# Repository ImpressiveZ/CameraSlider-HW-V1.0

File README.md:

# CameraSlider-HW-V1.0
滑轨电路板KiCAD工程，V1.0

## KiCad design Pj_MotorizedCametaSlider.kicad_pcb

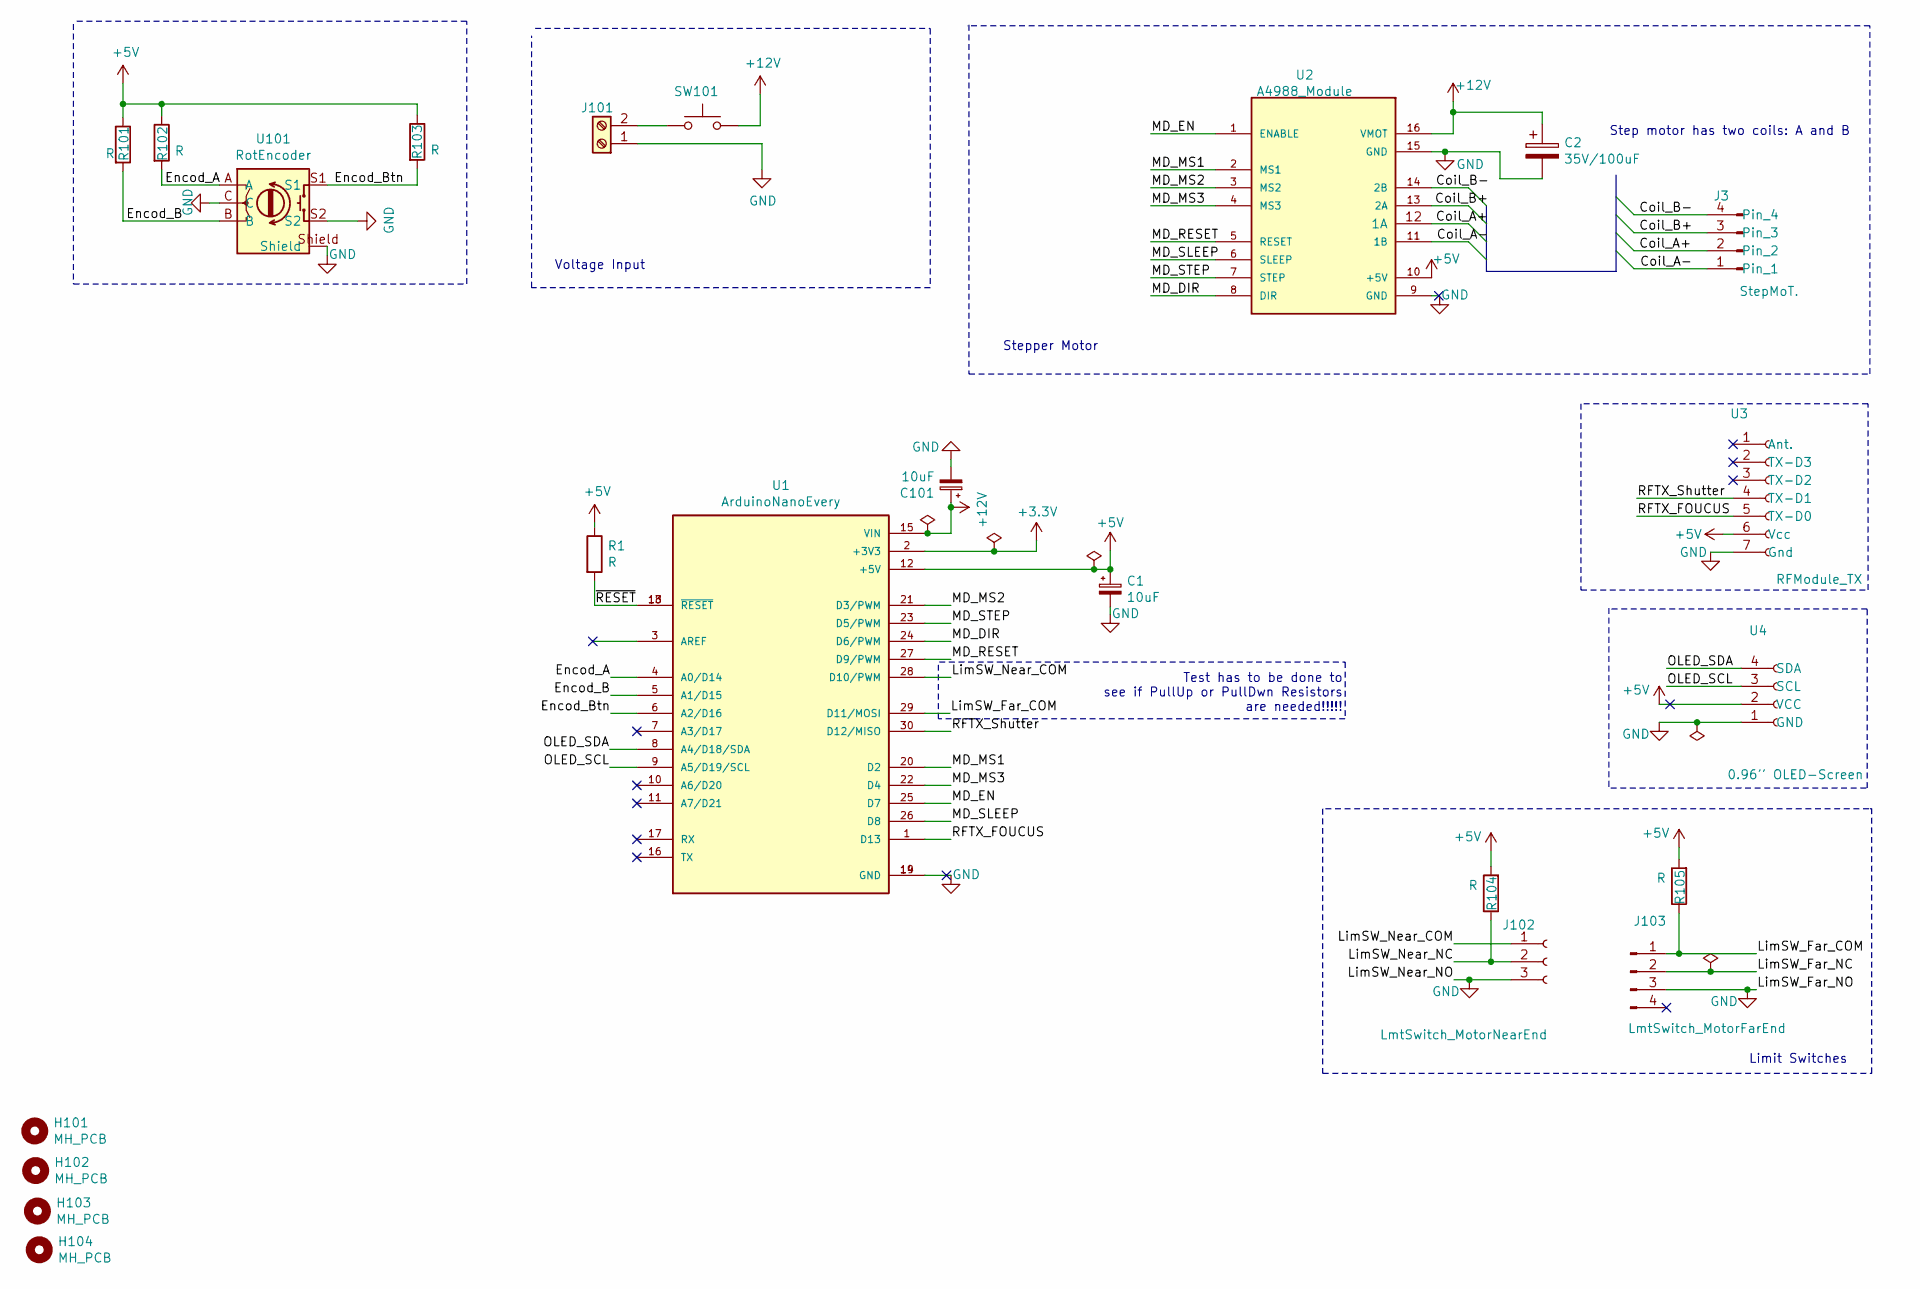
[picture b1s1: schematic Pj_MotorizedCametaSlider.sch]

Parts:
C1, C101: 10uF; CP_Radial_D5.0mm_P2.50mm
C2: 35V/100uF; CP_Radial_D5.0mm_P2.50mm
H101, H102, H103, H104: MH_PCB; MountingHole_3.2mm_M3
J3: StepMoT.; Molex_SPOX_4Pol
J101: Screw_Terminal_01x02; PhoenixContact_MCV_1,5_2-G-5.08_1x02_P5.08mm_Vertical
J102: LmtSwitch_MotorNearEnd; LimitSwitch_3-Pin_MH-included
J103: LmtSwitch_MotorFarEnd; PinHeader_1x04_P2.54mm_Vertical
R1, R101, R102, R103, R104, R105: R; R_0805_2012Metric_Pad1.20x1.40mm_HandSolder
SW101: SW_Push; SW_E-Switch_EG1271_DPDT
U1: ArduinoNanoEvery; MODULE_ArduinoNanoEvery; PARTREV 6-11-19
U2: A4988_Module; Module_A4988
U3: RFModule_TX; PinSocket_1x07_P2.54mm_Vertical
U4: 0.96'' OLED-Screen; 0.96-OLED
U101: RotEncoder

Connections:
+3V3: U1.2 (+3V3)
+5V: C1.1, R1.1, R101.1, R102.1, R103.1, R104.2, R105.2, U1.12 (+5V), U2.10 (+5V), U3.6 (Vcc), U4.2 (VCC)
+12V: C2.1, C101.1, SW101.2, U1.15 (VIN), U2.16 (VMOT); also elsewhere on the board
/Coil_A+: J3.2, U2.12 (1A)
/Coil_A-: J3.1, U2.11 (1B)
/Coil_B+: J3.3, U2.13 (2A)
/Coil_B-: J3.4, U2.14 (2B)
/Encod_A: R102.2, U1.4 (A0/D14), U101.A
/Encod_B: R101.2, U1.5 (A1/D15), U101.B
/Encod_Btn: R103.2, U1.6 (A2/D16), U101.S1
/LimSW_Far_COM: J103.1, R105.1, U1.29 (D11/MOSI)
/LimSW_Far_NC: J103.2
/LimSW_Near_COM: J102.1 (COM), U1.28 (D10/PWM)
/LimSW_Near_NC: J102.2 (NC), R104.1
/MD_DIR: U1.24 (D6/PWM), U2.8 (DIR)
/MD_EN: U1.25 (D7), U2.1 (ENABLE)
/MD_MS1: U1.20 (D2), U2.2 (MS1)
/MD_MS2: U1.21 (D3/PWM), U2.3 (MS2)
/MD_MS3: U1.22 (D4), U2.4 (MS3)
/MD_RESET: U1.27 (D9/PWM), U2.5 (RESET)
/MD_SLEEP: U1.26 (D8), U2.6 (SLEEP)
/MD_STEP: U1.23 (D5/PWM), U2.7 (STEP)
/OLED_SCL: U1.9 (A5/D19/SCL), U4.3 (SCL)
/OLED_SDA: U1.8 (A4/D18/SDA), U4.4 (SDA)
/RFTX_FOUCUS: U1.1 (D13), U3.5 (TX-D0)
/RFTX_Shutter: U1.30 (D12/MISO), U3.4 (TX-D1)
/~RESET: R1.2, U1.13 (~RESET), U1.18 (~RESET)
GND: C1.2, C2.2, C101.2, J101.1, J102.3 (NO), J103.3, U1.14 (GND), U1.19 (GND), U2.9 (GND), U2.15 (GND), U3.7 (Gnd), U4.1 (GND), U101.C, U101.S2, U101.Shield
unnamed 28: J101.2, SW101.1; also elsewhere on the board

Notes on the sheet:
Step motor has two coils: A and B
Voltage Input
Stepper Motor
Test has to be done to see if PullUp or PullDwn Resistors are needed!!!!!
Limit Switches

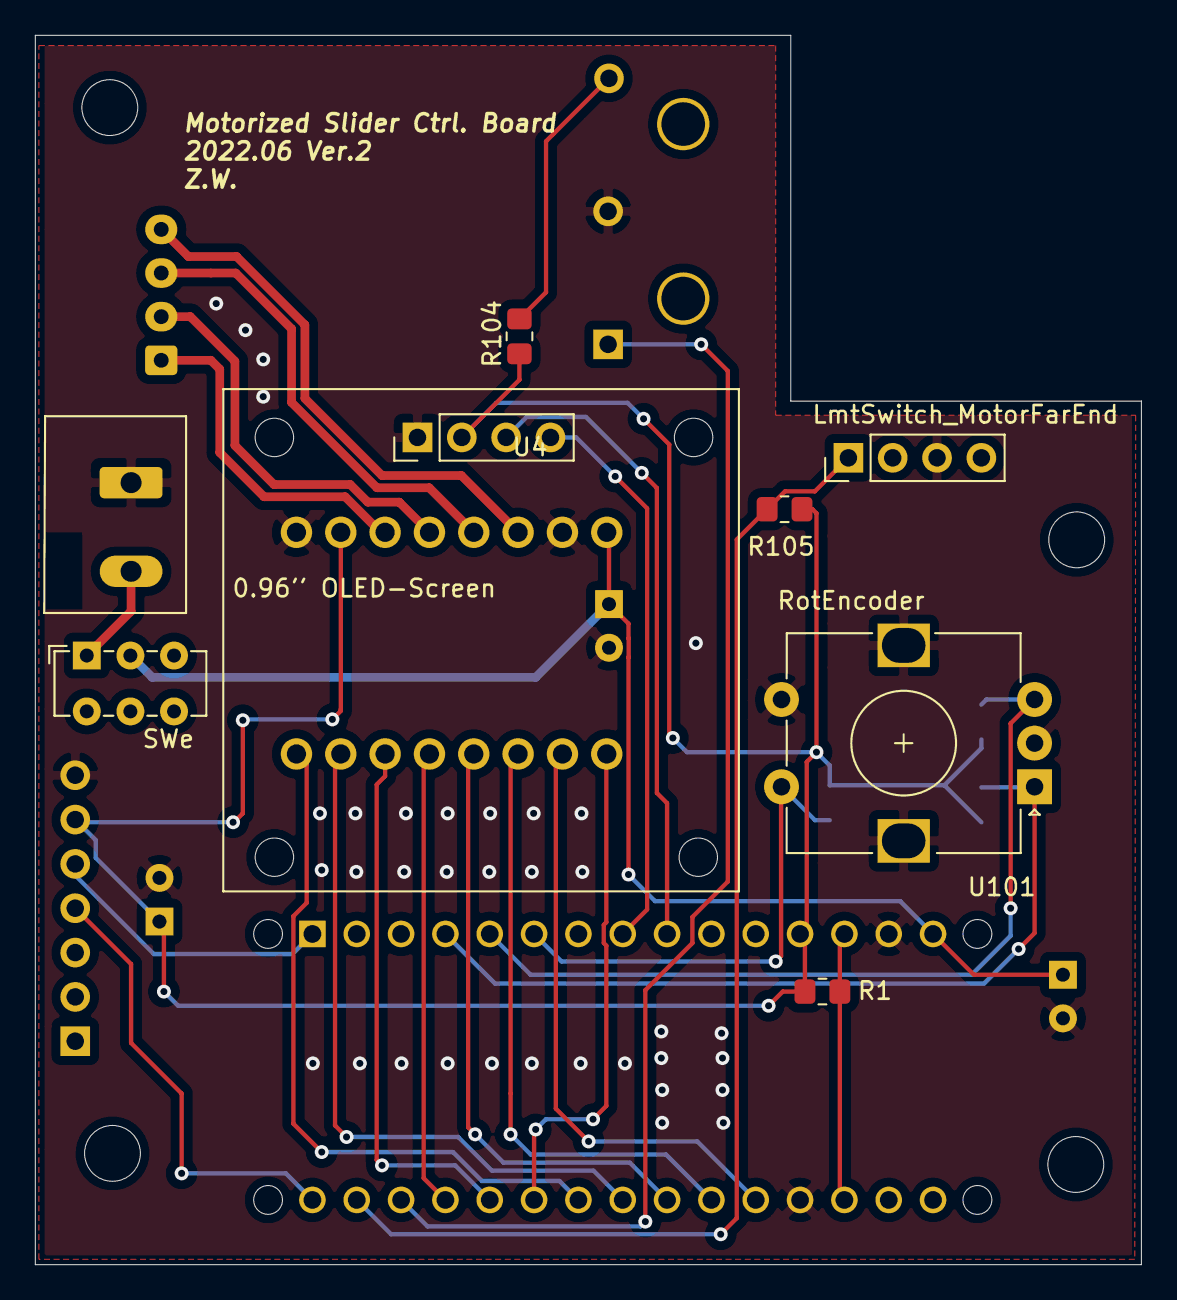
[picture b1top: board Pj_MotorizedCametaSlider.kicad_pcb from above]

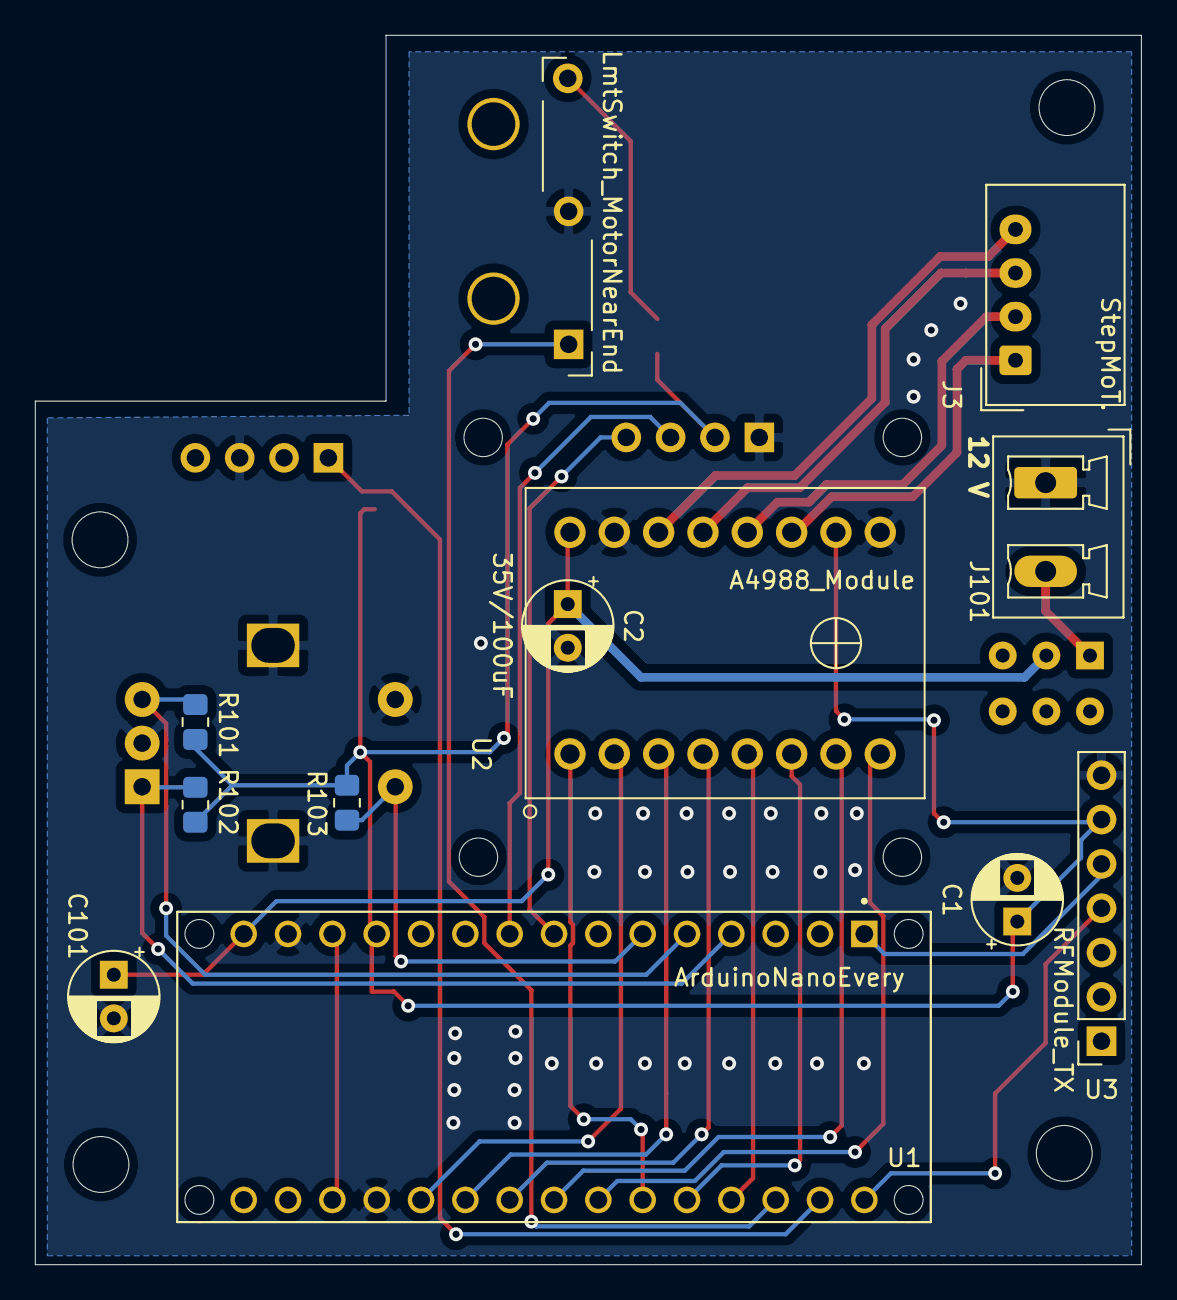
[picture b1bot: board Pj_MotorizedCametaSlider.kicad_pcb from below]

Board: 2 copper layers, 63.4 x 70.4 mm, 23 parts (12 on the bottom side), 27 nets.

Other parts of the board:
SWe: SW_Push; SW_E-Switch_EG1271_DPDT

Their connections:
+12V: SWe.2; also elsewhere on the board
unnamed 28: SWe.1; also elsewhere on the board
